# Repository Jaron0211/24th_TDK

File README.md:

creat time:20191126
this project is for 24th TDK

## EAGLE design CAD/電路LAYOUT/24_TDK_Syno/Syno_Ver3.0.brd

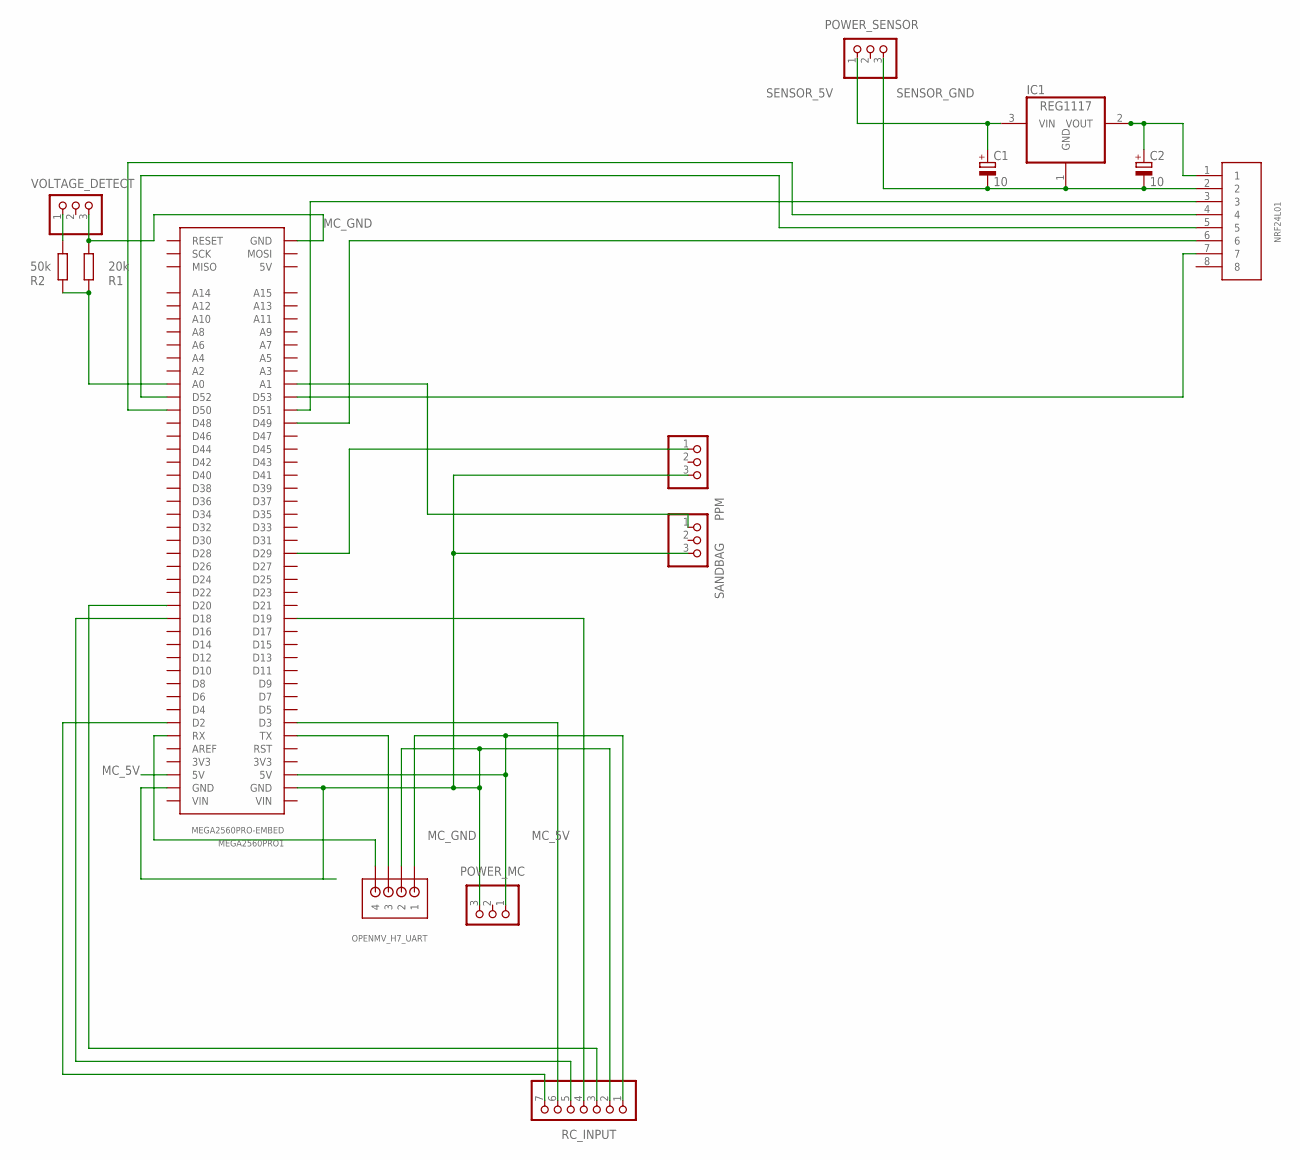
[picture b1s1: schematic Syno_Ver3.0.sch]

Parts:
C1, C2: 10; E1,8-4
IC1: REG1117; SOT223
MEGA2560PRO1: MEGA2560PRO-EMBED
NRF24L01: 8PIN; B8B-PH-K-S
OPENMV_H7_UART: JST-PH_4-PIN_HEADER; JST_B4B-PH_HEADER
POWER_MC: PINHD-1X3/90; 1X03/90
POWER_SENSOR: PINHD-1X3/90; 1X03/90
PPM: PINHD-1X3/90; 1X03/90
R1: 20k; 0204/5
R2: 50k; 0204/5
RC_INPUT: PINHD-1X7/90; 1X07/90
SANDBAG: PINHD-1X3/90; 1X03/90
VOLTAGE_DETECT: PINHD-1X3/90; 1X03/90

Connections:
MC_5V: MEGA2560PRO1.5V@1 (5V), MEGA2560PRO1.5V@2 (5V), OPENMV_H7_UART.P1 (1), POWER_MC.1, RC_INPUT.1
MC_GND: MEGA2560PRO1.GND@1 (GND), MEGA2560PRO1.GND@2 (GND), MEGA2560PRO1.GND@3 (GND), OPENMV_H7_UART.P2 (2), POWER_MC.3, PPM.3, R1.1, RC_INPUT.2, SANDBAG.3, VOLTAGE_DETECT.3
unnamed: MEGA2560PRO1.D2, RC_INPUT.7
unnamed: MEGA2560PRO1.D3, RC_INPUT.6
unnamed: C2.+, IC1.2 (VOUT), NRF24L01.1
unnamed: MEGA2560PRO1.D18, RC_INPUT.5
unnamed: MEGA2560PRO1.D19, RC_INPUT.4
unnamed: R2.1, VOLTAGE_DETECT.1
unnamed: MEGA2560PRO1.A0, R1.2, R2.2
unnamed: MEGA2560PRO1.TX, OPENMV_H7_UART.P3 (3)
unnamed: MEGA2560PRO1.RX, OPENMV_H7_UART.P4 (4)
unnamed: MEGA2560PRO1.D51, NRF24L01.3
unnamed: MEGA2560PRO1.D50, NRF24L01.4
unnamed: MEGA2560PRO1.D52, NRF24L01.5
unnamed: MEGA2560PRO1.D20, RC_INPUT.3
unnamed: MEGA2560PRO1.D49, NRF24L01.6
unnamed: MEGA2560PRO1.D53, NRF24L01.7
unnamed: MEGA2560PRO1.D29, PPM.1
unnamed: MEGA2560PRO1.A1, SANDBAG.1
SENSOR_5V: C1.+, IC1.3 (VIN), POWER_SENSOR.1
SENSOR_GND: C1.-, C2.-, IC1.1 (GND), NRF24L01.2, POWER_SENSOR.3

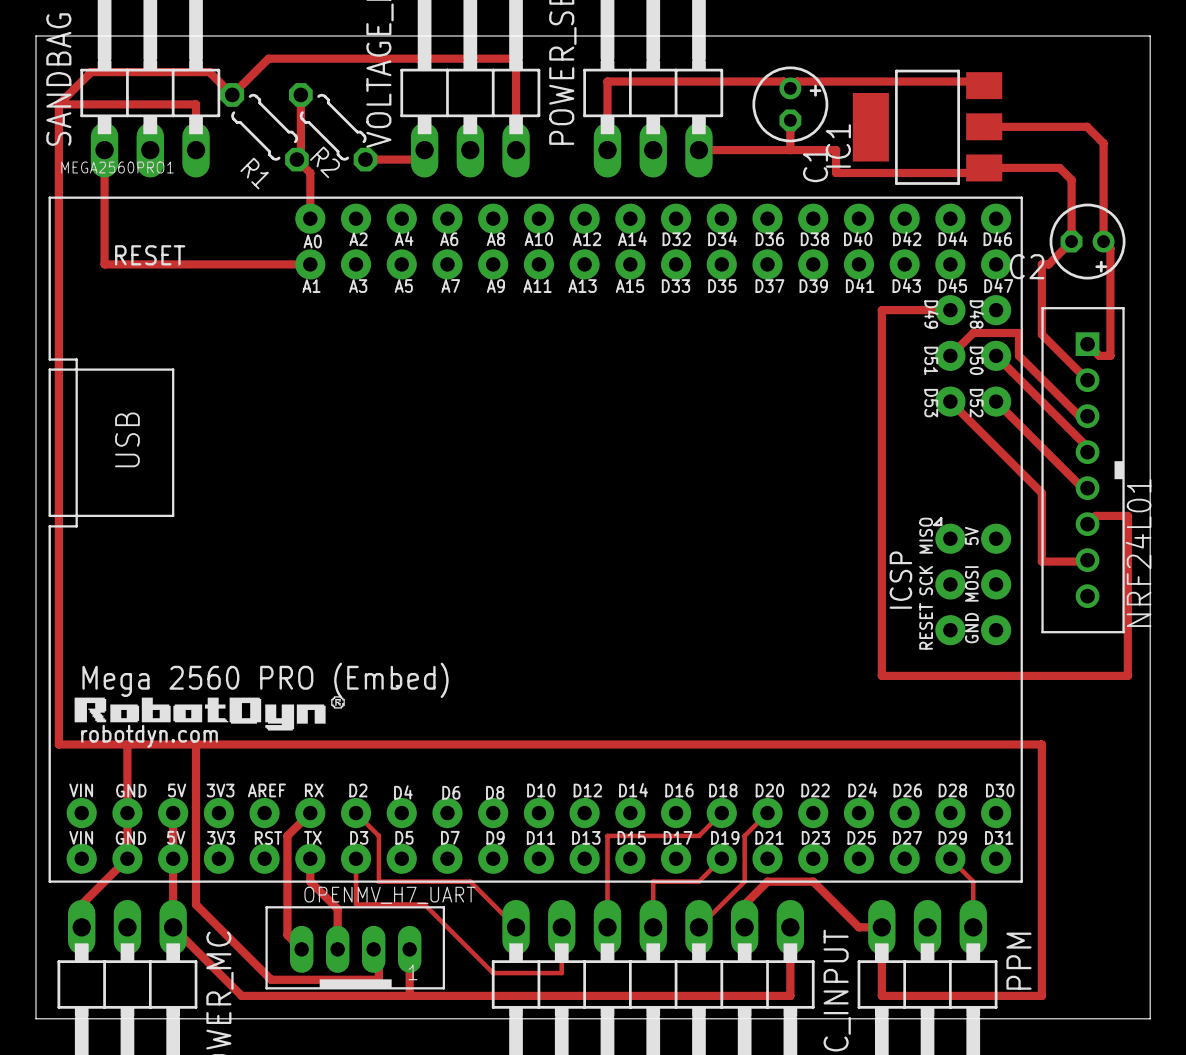
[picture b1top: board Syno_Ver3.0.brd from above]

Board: 2 copper layers, 61.9 x 54.6 mm, 14 parts (0 on the bottom side), 21 nets.

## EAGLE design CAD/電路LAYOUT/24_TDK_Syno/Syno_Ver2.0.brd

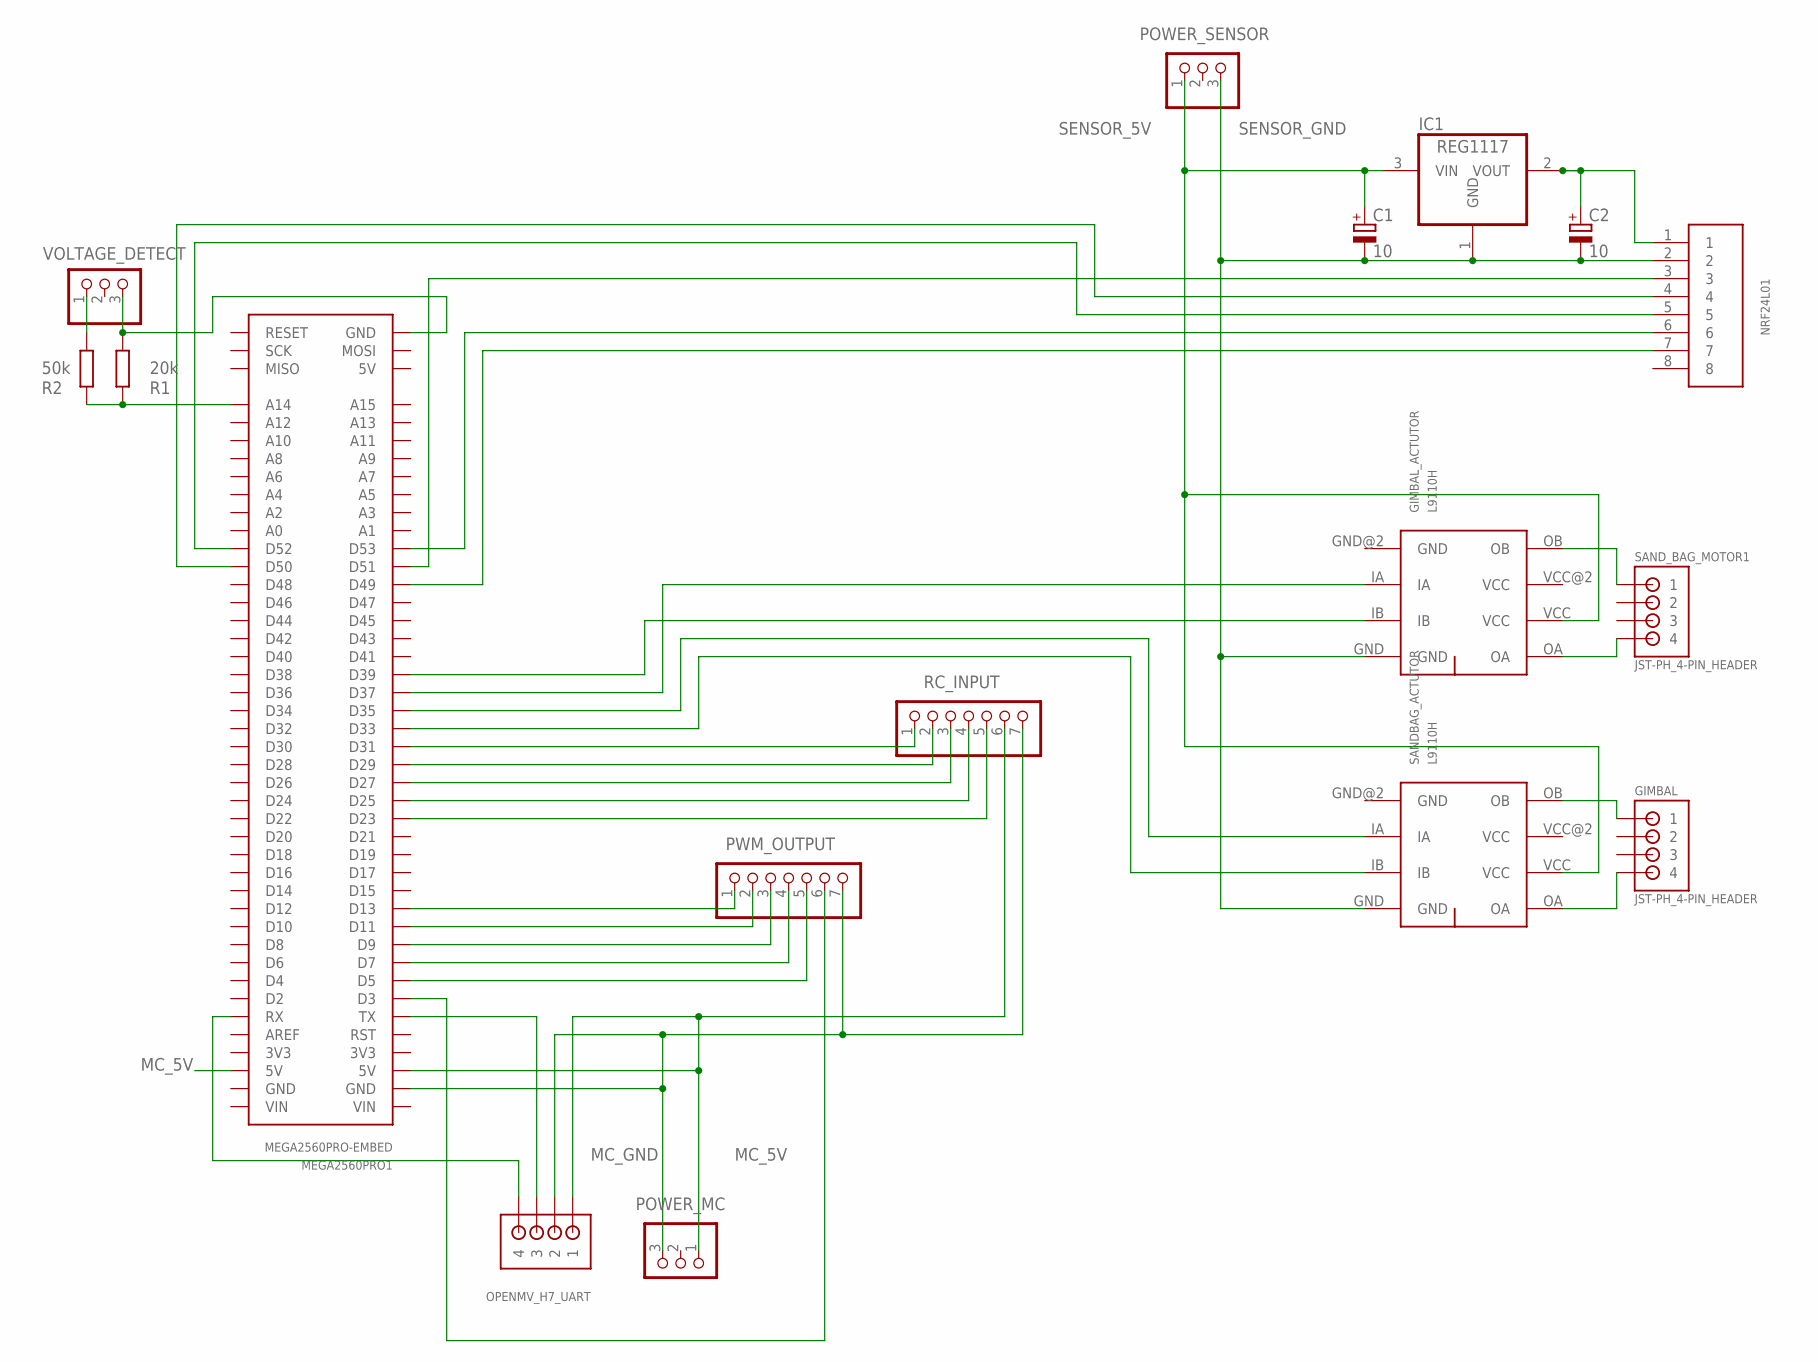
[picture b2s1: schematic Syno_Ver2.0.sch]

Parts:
C1, C2: 10; E1,8-4
GIMBAL: JST-PH_4-PIN_HEADER; JST_B4B-PH_HEADER
GIMBAL_ACTUTOR: L9110H
IC1: REG1117; SOT223
MEGA2560PRO1: MEGA2560PRO-EMBED
NRF24L01: 8PIN; B8B-PH-K-S
OPENMV_H7_UART: JST-PH_4-PIN_HEADER; JST_B4B-PH_HEADER
POWER_MC: PINHD-1X3/90; 1X03/90
POWER_SENSOR: PINHD-1X3/90; 1X03/90
PWM_OUTPUT: PINHD-1X7/90; 1X07/90
R1: 20k; 0204/5
R2: 50k; 0204/5
RC_INPUT: PINHD-1X7/90; 1X07/90
SANDBAG_ACTUTOR: L9110H
SAND_BAG_MOTOR1: JST-PH_4-PIN_HEADER; JST_B4B-PH_HEADER
VOLTAGE_DETECT: PINHD-1X3/90; 1X03/90

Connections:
GND: GIMBAL_ACTUTOR.GND@2 (GND), SANDBAG_ACTUTOR.GND@2 (GND)
MC_5V: MEGA2560PRO1.5V@1 (5V), MEGA2560PRO1.5V@2 (5V), OPENMV_H7_UART.P1 (1), POWER_MC.1, RC_INPUT.6
MC_GND: MEGA2560PRO1.GND@1 (GND), OPENMV_H7_UART.P2 (2), POWER_MC.3, PWM_OUTPUT.7, RC_INPUT.7
unnamed: GIMBAL_ACTUTOR.OB, SAND_BAG_MOTOR1.P1 (1)
unnamed: GIMBAL_ACTUTOR.OA, SAND_BAG_MOTOR1.P4 (4)
unnamed: C2.+, IC1.2 (VOUT), NRF24L01.1
unnamed: GIMBAL.P1 (1), SANDBAG_ACTUTOR.OB
unnamed: GIMBAL.P4 (4), SANDBAG_ACTUTOR.OA
unnamed: R2.1, VOLTAGE_DETECT.1
unnamed: MEGA2560PRO1.A14, R1.2, R2.2
unnamed: MEGA2560PRO1.GND@3 (GND), R1.1, VOLTAGE_DETECT.3
unnamed: MEGA2560PRO1.TX, OPENMV_H7_UART.P3 (3)
unnamed: MEGA2560PRO1.RX, OPENMV_H7_UART.P4 (4)
unnamed: MEGA2560PRO1.D51, NRF24L01.3
unnamed: MEGA2560PRO1.D50, NRF24L01.4
unnamed: MEGA2560PRO1.D52, NRF24L01.5
unnamed: MEGA2560PRO1.D3, PWM_OUTPUT.6
unnamed: MEGA2560PRO1.D5, PWM_OUTPUT.5
unnamed: MEGA2560PRO1.D7, PWM_OUTPUT.4
unnamed: MEGA2560PRO1.D9, PWM_OUTPUT.3
unnamed: MEGA2560PRO1.D11, PWM_OUTPUT.2
unnamed: MEGA2560PRO1.D13, PWM_OUTPUT.1
unnamed: MEGA2560PRO1.D23, RC_INPUT.5
unnamed: MEGA2560PRO1.D25, RC_INPUT.4
unnamed: MEGA2560PRO1.D27, RC_INPUT.3
unnamed: MEGA2560PRO1.D29, RC_INPUT.2
unnamed: MEGA2560PRO1.D31, RC_INPUT.1
unnamed: MEGA2560PRO1.D53, NRF24L01.6
unnamed: MEGA2560PRO1.D49, NRF24L01.7
unnamed: GIMBAL_ACTUTOR.IA, MEGA2560PRO1.D37
unnamed: GIMBAL_ACTUTOR.IB, MEGA2560PRO1.D39
unnamed: MEGA2560PRO1.D35, SANDBAG_ACTUTOR.IA
unnamed: MEGA2560PRO1.D33, SANDBAG_ACTUTOR.IB
SENSOR_5V: C1.+, GIMBAL_ACTUTOR.VCC, IC1.3 (VIN), POWER_SENSOR.1, SANDBAG_ACTUTOR.VCC
SENSOR_GND: C1.-, C2.-, GIMBAL_ACTUTOR.GND, IC1.1 (GND), NRF24L01.2, POWER_SENSOR.3, SANDBAG_ACTUTOR.GND
VCC: GIMBAL_ACTUTOR.VCC@2 (VCC), SANDBAG_ACTUTOR.VCC@2 (VCC)

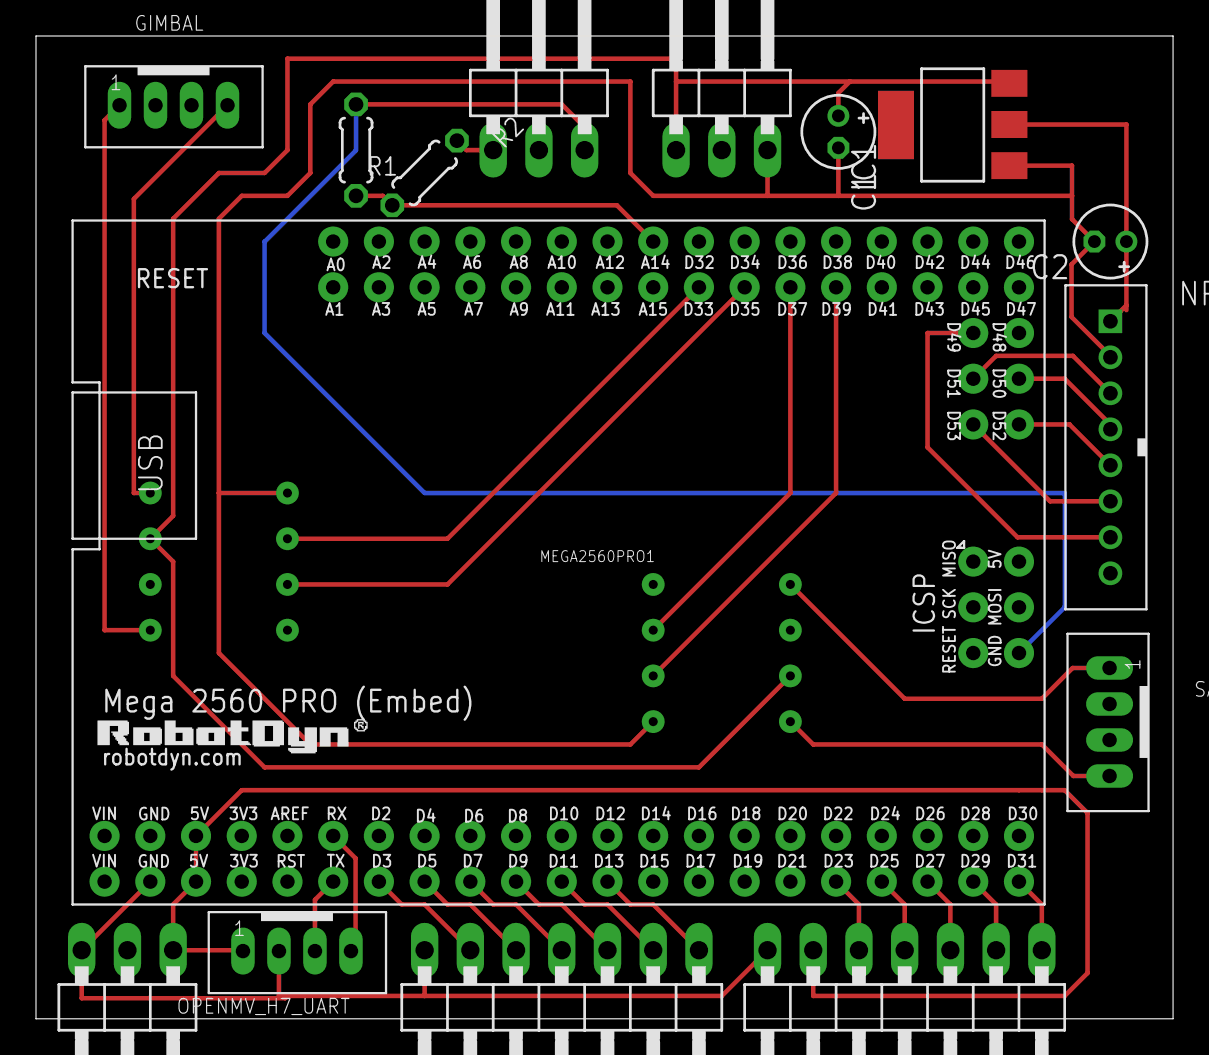
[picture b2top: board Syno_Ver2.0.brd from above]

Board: 2 copper layers, 63.2 x 54.6 mm, 17 parts (0 on the bottom side), 36 nets.

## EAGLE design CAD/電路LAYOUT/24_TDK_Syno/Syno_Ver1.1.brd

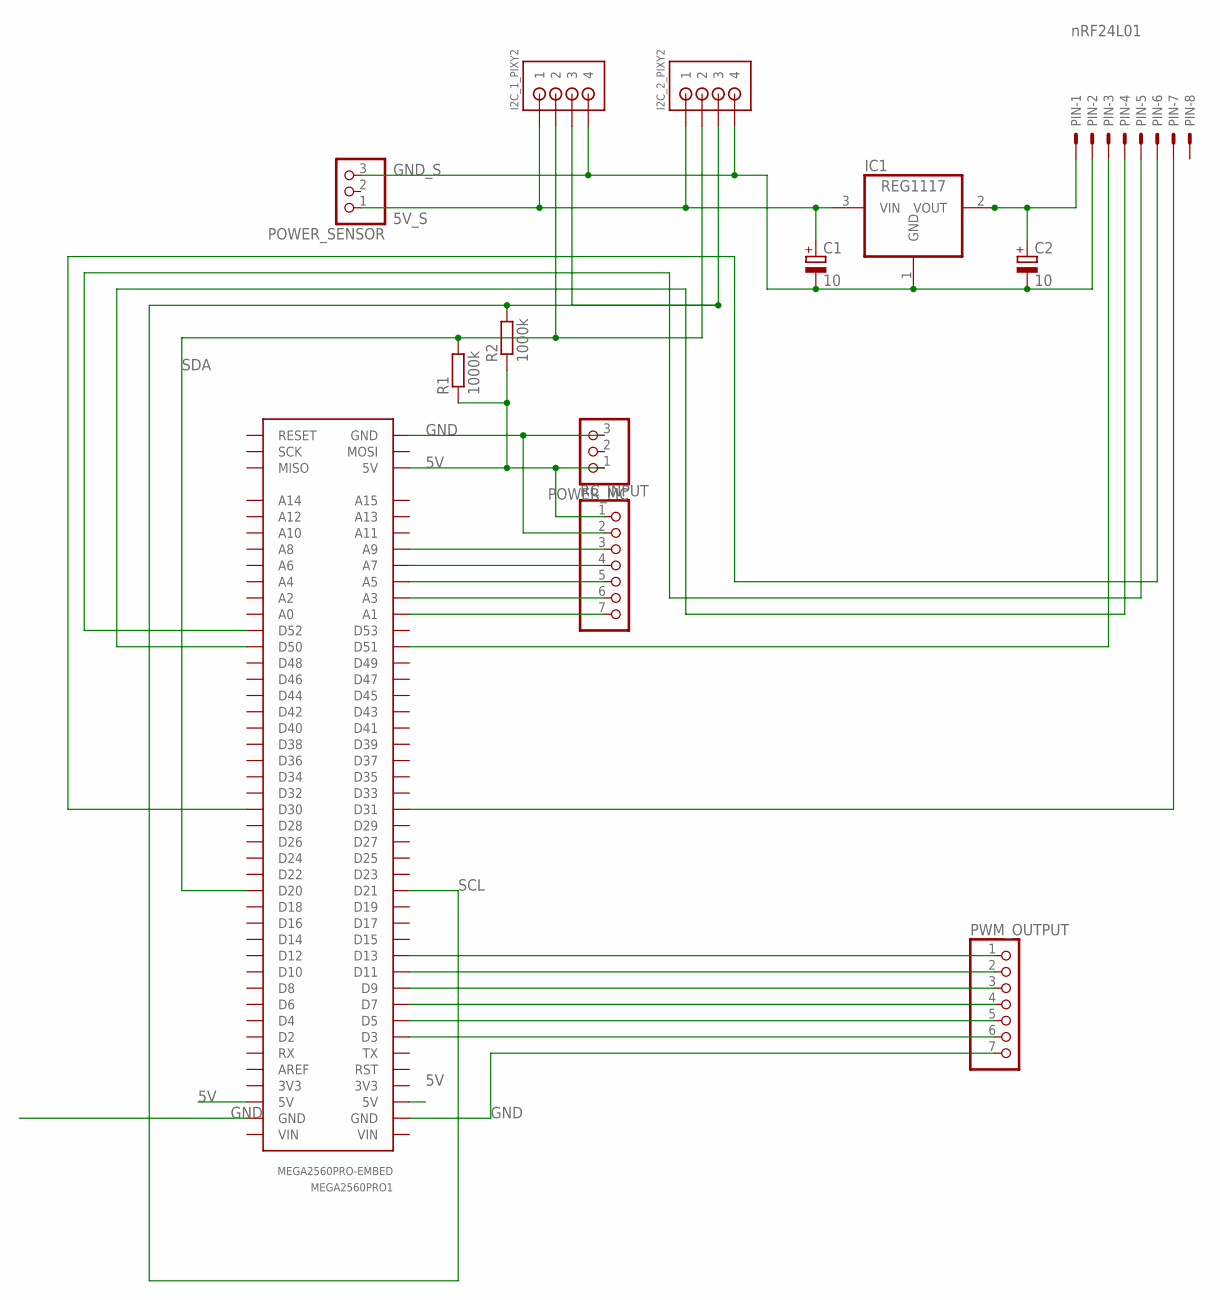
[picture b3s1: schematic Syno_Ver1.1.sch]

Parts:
C1, C2: 10; E1,8-4
I2C_1_PIXY2, I2C_2_PIXY2: JST-PH_4-PIN_HEADER; JST_B4B-PH_HEADER
IC1: REG1117; SOT223
MEGA2560PRO1: MEGA2560PRO-EMBED
PIN: nRF24L01; JST-XH-08-PACKAGE-ROUND-PAD
POWER_MC: PINHD-1X3/90; 1X03/90
POWER_SENSOR: PINHD-1X3/90; 1X03/90
PWM_OUTPUT: PINHD-1X7/90; 1X07/90
R1, R2: 1000k; 0204/5
RC_INPUT: PINHD-1X7/90; 1X07/90

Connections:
5V: MEGA2560PRO1.5V@1 (5V), MEGA2560PRO1.5V@2 (5V), MEGA2560PRO1.5V@3 (5V), POWER_MC.1, R1.1, R2.1, RC_INPUT.1
5V_S: C1.+, I2C_1_PIXY2.P1 (1), I2C_2_PIXY2.P1 (1), IC1.3 (VIN), POWER_SENSOR.1
GND: MEGA2560PRO1.GND@1 (GND), MEGA2560PRO1.GND@2 (GND), MEGA2560PRO1.GND@3 (GND), POWER_MC.3, PWM_OUTPUT.7, RC_INPUT.2
GND_S: C1.-, C2.-, I2C_1_PIXY2.P4 (4), I2C_2_PIXY2.P4 (4), IC1.1 (GND), PIN.2, POWER_SENSOR.3
unnamed: MEGA2560PRO1.D51, PIN.3
unnamed: C2.+, IC1.2 (VOUT), PIN.1
unnamed: MEGA2560PRO1.D50, PIN.4
unnamed: MEGA2560PRO1.D52, PIN.5
unnamed: MEGA2560PRO1.D30, PIN.6
unnamed: MEGA2560PRO1.D31, PIN.7
unnamed: MEGA2560PRO1.D13, PWM_OUTPUT.1
unnamed: MEGA2560PRO1.D11, PWM_OUTPUT.2
unnamed: MEGA2560PRO1.D9, PWM_OUTPUT.3
unnamed: MEGA2560PRO1.D7, PWM_OUTPUT.4
unnamed: MEGA2560PRO1.D5, PWM_OUTPUT.5
unnamed: MEGA2560PRO1.D3, PWM_OUTPUT.6
unnamed: MEGA2560PRO1.A9, RC_INPUT.3
unnamed: MEGA2560PRO1.A7, RC_INPUT.4
unnamed: MEGA2560PRO1.A5, RC_INPUT.5
unnamed: MEGA2560PRO1.A3, RC_INPUT.6
unnamed: MEGA2560PRO1.A1, RC_INPUT.7
SCL: I2C_1_PIXY2.P3 (3), I2C_2_PIXY2.P3 (3), MEGA2560PRO1.D21, R2.2
SDA: I2C_1_PIXY2.P2 (2), I2C_2_PIXY2.P2 (2), MEGA2560PRO1.D20, R1.2

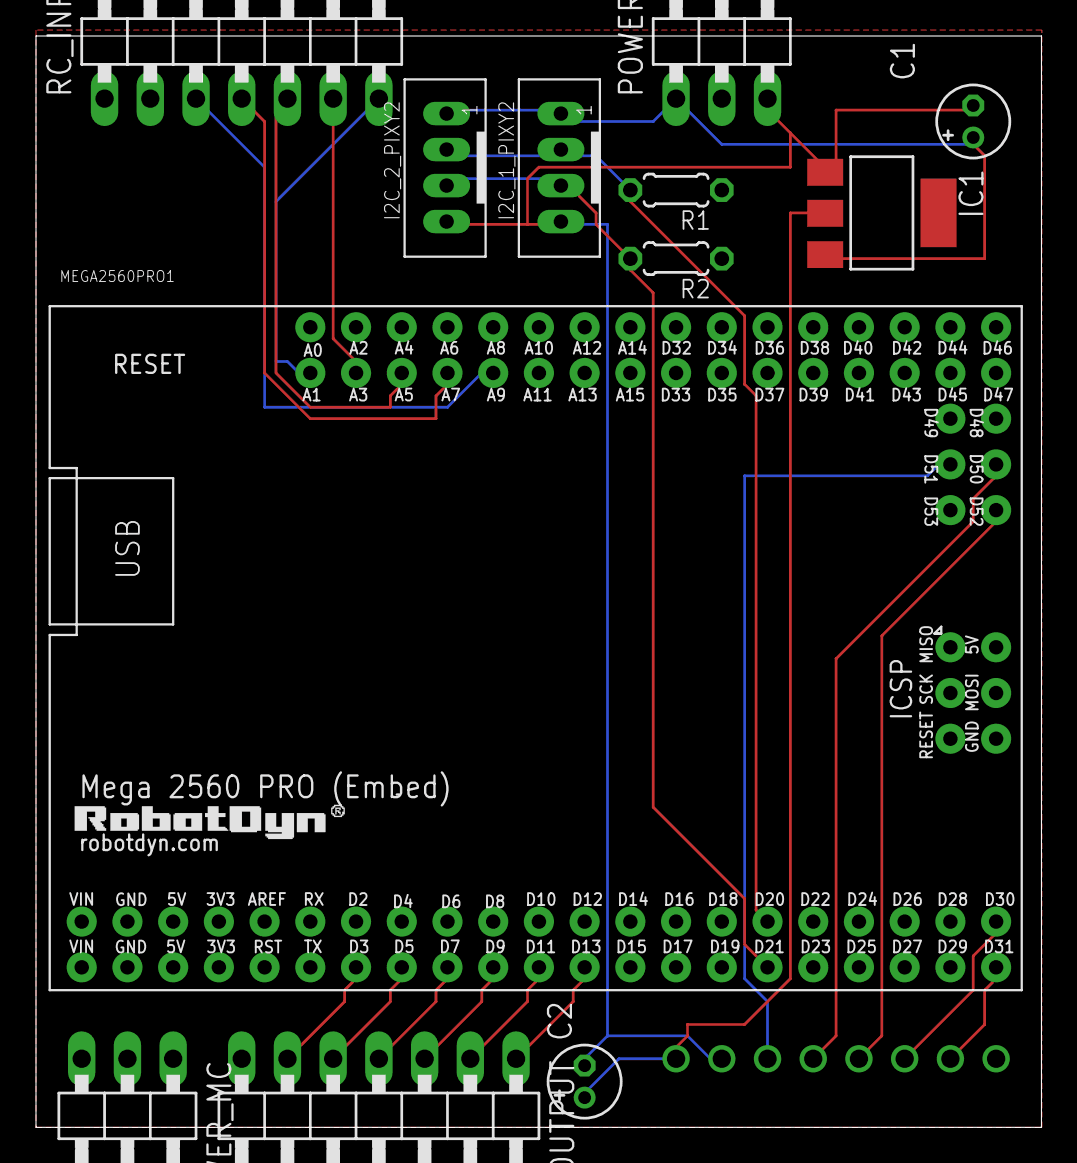
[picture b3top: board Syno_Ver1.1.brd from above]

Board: 2 copper layers, 55.9 x 60.6 mm, 13 parts (1 on the bottom side), 23 nets.

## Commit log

2019-11-26 Create test.txt
    for test
2019-11-26 add
    remove the test.txt and add the README.ed file
2019-11-26 Revert "add"
    This reverts commit 139ea8ac5216c5ed4ecdb46d2c3d4d7fe438ad2b.
2019-11-26 Revert "Revert "add""
    This reverts commit 4aecb3f94d1fe287c40ef65bc1487e6a9c08a3a3.
2020-01-17 daliy update
    新增文件資料
2020-01-18 資料庫更新與新增
    202010118
    新增CAD電路Layout
2020-01-19 daily update
    整理檔案與更新電路Layout(1.0~1.2)
2020-01-21 daily update
    新增正式的程式，與debug用的header.md file,
2020-01-21 working update
    save
2020-01-21 layout update
    完成Layout更新
2020-02-21 data update
    added openmv h7 CAD file
2020-02-21 daily update
    add 生力計算機
2020-02-23 daily update
    update syno_0.0.1 software, add some basic feature and create -- tag to quick debugging , but there some software things need to add , PWM SIGNAL RANGE , OPENMV SENSOR DATA REGONIZE. those should be 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
2020-02-25 daily update
    update syno, add syno_r data struction
2020-02-25 Update syno-r_0.0.1.ino
    now is also work by Serial output to PC
2020-02-27 daily update
    finish syno broad design
2020-03-02 daily update
    update syno_v2.0 schemetic
2020-03-09 daily update
    daily update
2020-03-09 desktop update
    upload desktop file to the cloud
2020-03-15 daily update
    finish the main frame core component
2020-03-15 daily update
    update the gimbal model
2020-03-22 weekly update
2020-03-25 daily update
    update some pic
2020-03-31 daily update
    update syno system, Pixhawk version syno,now can convert PWM single to PPM
2020-03-31 daily update
2020-03-31 daily work
    update syno software
2020-04-11 daily update
    work update
